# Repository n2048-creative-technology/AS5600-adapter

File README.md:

# AS5600-adapter

A tiny breakout PCB that re-maps the AS5600 magnetic angle sensor module's
awkward pin layout onto a standard, easier-to-wire 1x4 header — commonly
sold AS5600 boards break out `VCC/GND/SCL/SDA` (plus OUT/DIR pins) in an
order that doesn't play well with standard jumper cables or a solderless
breadboard.

## What it is

A passive adapter PCB (no active components) with two headers:

- `J1`/`J3` — 1x4 pin headers
- `J2` — 1x3 pin header

Populate per the BOM below and mount the commercial AS5600 module on one
side; the adapter re-orders its pins to a clean pinout on the other side.
See `encoder-adapter.kicad_sch` / `encoder-adapter.kicad_pcb` for the exact
net mapping if you need to confirm pin-for-pin before soldering.

## Bill of materials

From [`production/bom.csv`](production/bom.csv):

| Designator | Footprint | Qty | Value |
|---|---|---|---|
| J1, J3 | PinHeader 1x04, 2.54mm, vertical | 2 | Conn_01x04 |
| J2 | PinHeader 1x03, 2.54mm, vertical | 1 | Conn_01x03 |

## Fabrication

`production/` contains the JLCPCB-ready gerbers, drill files, BOM and
pick-and-place (`encoder-adapter.zip`) — upload that zip directly to
JLCPCB, PCBWay, or similar. The board is 2-layer, through-hole only, no
SMT assembly required.

## Use

Wire the AS5600 module to the adapter's headers per the KiCad schematic,
then use the adapter's re-ordered header to connect I2C (`SCL`/`SDA`) and
power to your microcontroller of choice — the AS5600 itself is a standard
I2C 12-bit magnetic angle sensor, addressable at `0x36`.

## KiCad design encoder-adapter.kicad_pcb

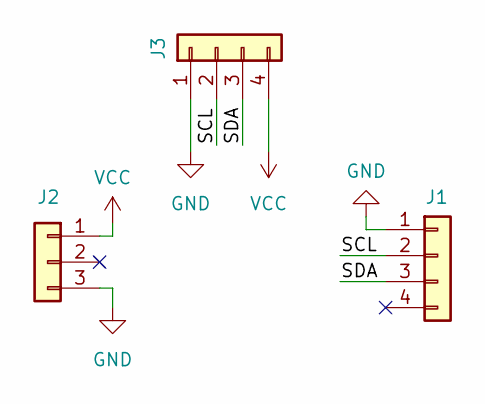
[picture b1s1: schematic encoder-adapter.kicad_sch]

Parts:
J1, J3: Conn_01x04; PinHeader_1x04_P2.54mm_Vertical
J2: Conn_01x03; PinHeader_1x03_P2.54mm_Vertical

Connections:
/SCL: J1.2, J3.2
/SDA: J1.3, J3.3
GND: J1.1, J2.3, J3.1
VCC: J2.1, J3.4

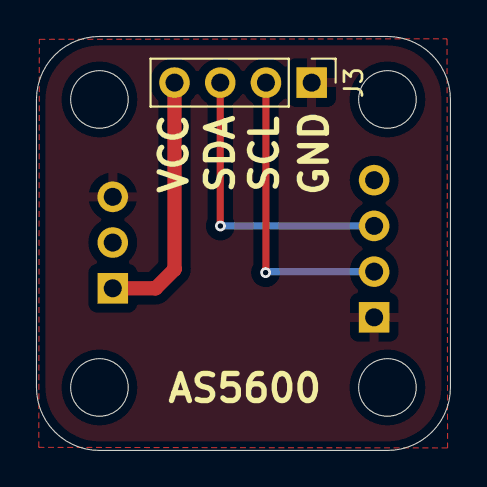
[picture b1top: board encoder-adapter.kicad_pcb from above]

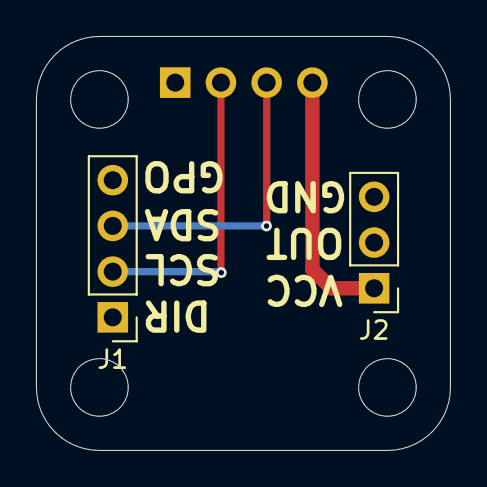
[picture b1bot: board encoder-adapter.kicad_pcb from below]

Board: 2 copper layers, 23.0 x 23.0 mm, 3 parts (2 on the bottom side), 4 nets.

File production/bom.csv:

Designator,Footprint,Quantity,Value,LCSC Part #
"J1, J3",PinHeader_1x04_P2.54mm_Vertical,2,Conn_01x04,
J2,PinHeader_1x03_P2.54mm_Vertical,1,Conn_01x03,
